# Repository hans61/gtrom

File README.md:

# Gigatron ROM Adapter
This is my first attempt for a simple ROM adapter for the Gigatron TTL. There are two good reasons for this.
The first is, there is no inexpensive ZIF socket that fits directly on the mainboard. If you use a turned socket on the mainboard and turned pins for the adapter, then it adds a ZIF socket to the Gigatron.
My second problem is that to test different software I often have to change the ROM. This is inconvenient because I have to remove the cover from my Gigatron case each time.
The adapter allows the use of a 256k x16 EPROM. This allows, via a switch or jumper, switching 4 different ROM's. 
One possible EPROM is the 27C4002. I found it in China and at the local dealer. (https://www.reichelt.de/eprom-4-mb-256-k-x-16-4-5-5-5-v-fdip-40-27c4002-100-p1930.html?&nbc=1)
In China I also found the W27C4096, a pin compatible EEPROM.

Theoretically, a simple ROM banking would also be possible in this way to extend the Gigatron ROM.

I have tested the ROM switch with the 27C4002. The 27C4002 can be programmed with the TL866II or successor devices. With both switches in the off position, the original Gigatron ROM can also be used.

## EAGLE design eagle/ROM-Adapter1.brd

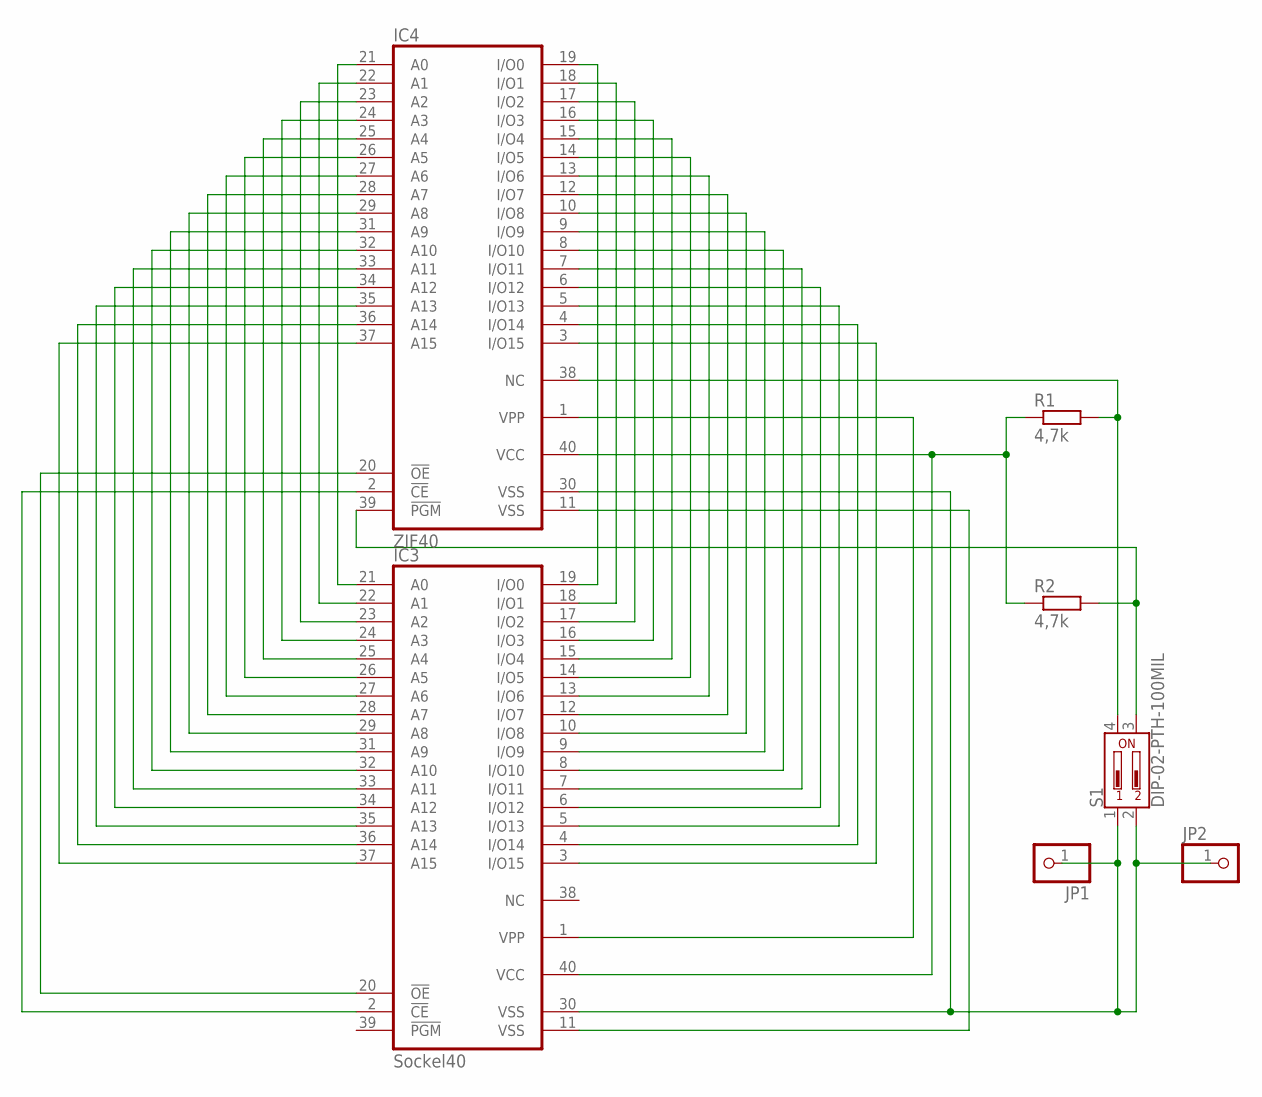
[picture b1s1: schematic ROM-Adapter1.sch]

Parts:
IC3: Sockel40; DIL40
IC4: ZIF40; MEMORY-HITACHI_ZIF40
JP1, JP2: PINHD-1X1; 1X01
R1, R2: 4,7k; 0207/10
S1: DIP-02-PTH-100MIL; DIPSWITCH-02-209-2LPST

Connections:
unnamed: IC3.21 (A0), IC4.21 (A0)
unnamed: IC3.22 (A1), IC4.22 (A1)
unnamed: IC3.23 (A2), IC4.23 (A2)
unnamed: IC3.24 (A3), IC4.24 (A3)
unnamed: IC3.25 (A4), IC4.25 (A4)
unnamed: IC3.26 (A5), IC4.26 (A5)
unnamed: IC3.27 (A6), IC4.27 (A6)
unnamed: IC3.28 (A7), IC4.28 (A7)
unnamed: IC3.29 (A8), IC4.29 (A8)
unnamed: IC3.31 (A9), IC4.31 (A9)
unnamed: IC3.32 (A10), IC4.32 (A10)
unnamed: IC3.33 (A11), IC4.33 (A11)
unnamed: IC3.34 (A12), IC4.34 (A12)
unnamed: IC3.35 (A13), IC4.35 (A13)
unnamed: IC3.36 (A14), IC4.36 (A14)
unnamed: IC3.37 (A15), IC4.37 (A15)
unnamed: IC3.20 (!OE), IC4.20 (!OE)
unnamed: IC3.2 (!CE), IC4.2 (!CE)
unnamed: IC4.38 (NC), R1.2, S1.4
unnamed: IC3.19 (I/O0), IC4.19 (I/O0)
unnamed: IC3.18 (I/O1), IC4.18 (I/O1)
unnamed: IC3.17 (I/O2), IC4.17 (I/O2)
unnamed: IC3.16 (I/O3), IC4.16 (I/O3)
unnamed: IC3.15 (I/O4), IC4.15 (I/O4)
unnamed: IC3.14 (I/O5), IC4.14 (I/O5)
unnamed: IC3.13 (I/O6), IC4.13 (I/O6)
unnamed: IC3.12 (I/O7), IC4.12 (I/O7)
unnamed: IC3.10 (I/O8), IC4.10 (I/O8)
unnamed: IC3.9 (I/O9), IC4.9 (I/O9)
unnamed: IC3.8 (I/O10), IC4.8 (I/O10)
unnamed: IC3.7 (I/O11), IC4.7 (I/O11)
unnamed: IC3.6 (I/O12), IC4.6 (I/O12)
unnamed: IC3.5 (I/O13), IC4.5 (I/O13)
unnamed: IC3.4 (I/O14), IC4.4 (I/O14)
unnamed: IC3.3 (I/O15), IC4.3 (I/O15)
unnamed: IC4.39 (!PGM), R2.2, S1.3
unnamed: IC3.1 (VPP), IC4.1 (VPP)
unnamed: IC3.40 (VCC), IC4.40 (VCC), R1.1, R2.1
unnamed: IC3.11 (VSS), IC4.11 (VSS)
unnamed: IC3.30 (VSS), IC4.30 (VSS), JP1.1, JP2.1, S1.1, S1.2

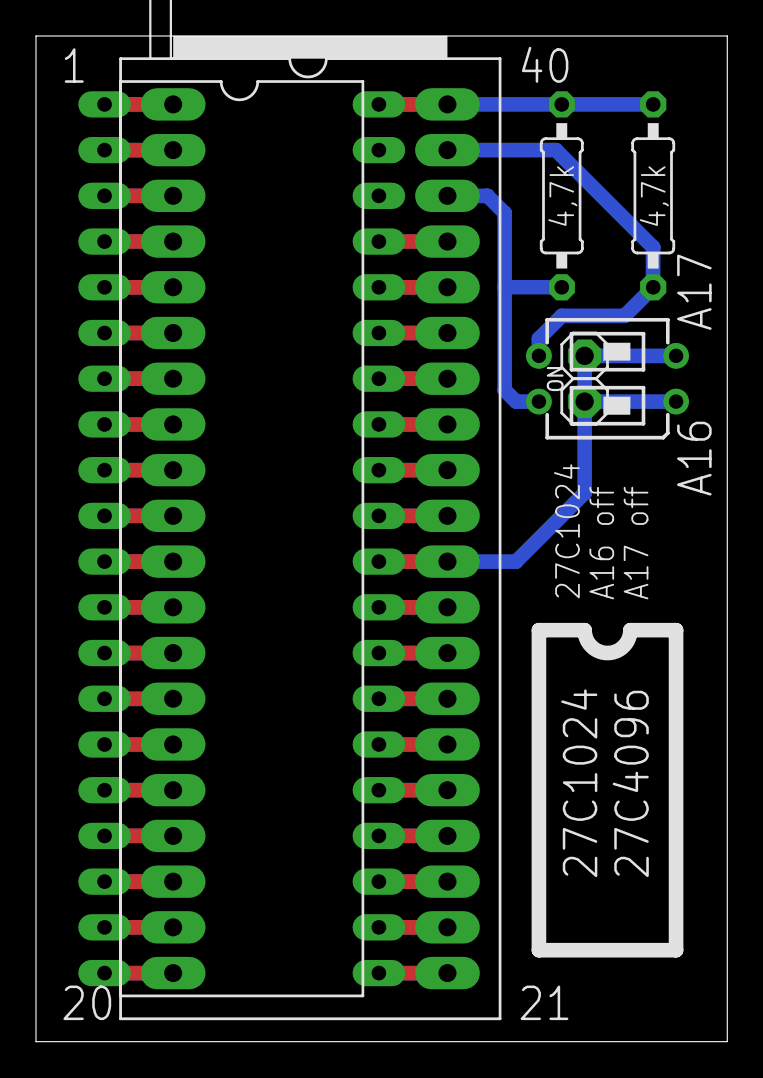
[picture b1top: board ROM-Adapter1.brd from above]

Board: 2 copper layers, 38.4 x 55.9 mm, 7 parts (0 on the bottom side), 40 nets.

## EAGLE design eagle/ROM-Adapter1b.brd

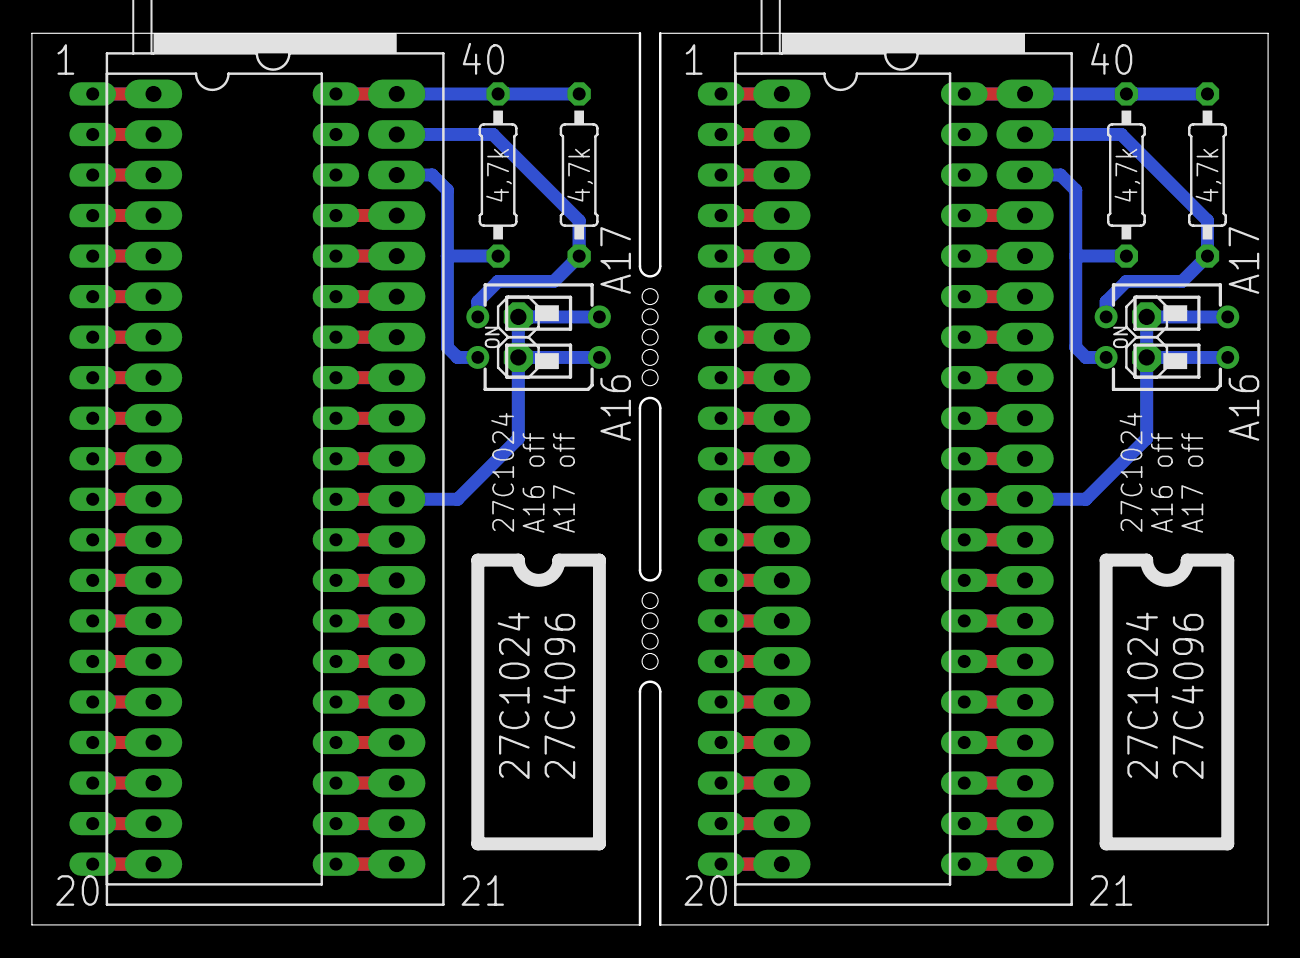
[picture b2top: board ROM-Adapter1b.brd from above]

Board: 2 copper layers, 77.5 x 55.9 mm, 14 parts (0 on the bottom side), 80 nets.

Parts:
IC1, IC3: Sockel40; DIL40
IC2, IC4: ZIF40; MEMORY-HITACHI_ZIF40
JP1, JP2, JP3, JP4: 1X01
R1, R2, R3, R4: 4,7k; 0207/10
S1, S2: DIP-02-PTH-100MIL; DIPSWITCH-02-209-2LPST

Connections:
unnamed: IC3.21, IC4.21
unnamed: IC3.22, IC4.22
unnamed: IC3.23, IC4.23
unnamed: IC3.24, IC4.24
unnamed: IC3.25, IC4.25
unnamed: IC3.26, IC4.26
unnamed: IC3.27, IC4.27
unnamed: IC3.28, IC4.28
unnamed: IC3.29, IC4.29
unnamed: IC3.31, IC4.31
unnamed: IC3.32, IC4.32
unnamed: IC3.33, IC4.33
unnamed: IC3.34, IC4.34
unnamed: IC3.35, IC4.35
unnamed: IC3.36, IC4.36
unnamed: IC3.37, IC4.37
unnamed: IC3.20, IC4.20
unnamed: IC3.2, IC4.2
unnamed: IC4.38, R1.2, S1.4
unnamed: IC3.19, IC4.19
unnamed: IC3.18, IC4.18
unnamed: IC3.17, IC4.17
unnamed: IC3.16, IC4.16
unnamed: IC3.15, IC4.15
unnamed: IC3.14, IC4.14
unnamed: IC3.13, IC4.13
unnamed: IC3.12, IC4.12
unnamed: IC3.10, IC4.10
unnamed: IC3.9, IC4.9
unnamed: IC3.8, IC4.8
unnamed: IC3.7, IC4.7
unnamed: IC3.6, IC4.6
unnamed: IC3.5, IC4.5
unnamed: IC3.4, IC4.4
unnamed: IC3.3, IC4.3
unnamed: IC4.39, R2.2, S1.3
unnamed: IC3.1, IC4.1
unnamed: IC3.40, IC4.40, R1.1, R2.1
unnamed: IC1.21, IC2.21
unnamed: IC3.11, IC4.11
unnamed: IC1.22, IC2.22
unnamed: IC3.30, IC4.30, JP1.1, JP2.1, S1.1, S1.2
unnamed: IC1.23, IC2.23
unnamed: IC1.24, IC2.24
unnamed: IC1.25, IC2.25
unnamed: IC1.26, IC2.26
unnamed: IC1.27, IC2.27
unnamed: IC1.28, IC2.28
unnamed: IC1.29, IC2.29
unnamed: IC1.31, IC2.31
unnamed: IC1.32, IC2.32
unnamed: IC1.33, IC2.33
unnamed: IC1.34, IC2.34
unnamed: IC1.35, IC2.35
unnamed: IC1.36, IC2.36
unnamed: IC1.37, IC2.37
unnamed: IC1.20, IC2.20
unnamed: IC1.2, IC2.2
unnamed: IC1.19, IC2.19
unnamed: IC1.18, IC2.18
unnamed: IC1.17, IC2.17
unnamed: IC1.16, IC2.16
unnamed: IC1.15, IC2.15
unnamed: IC1.14, IC2.14
unnamed: IC1.13, IC2.13
unnamed: IC1.12, IC2.12
unnamed: IC1.10, IC2.10
unnamed: IC1.9, IC2.9
unnamed: IC1.8, IC2.8
unnamed: IC1.7, IC2.7
unnamed: IC1.6, IC2.6
unnamed: IC1.5, IC2.5
unnamed: IC1.4, IC2.4
unnamed: IC1.3, IC2.3
unnamed: IC1.1, IC2.1
unnamed: IC1.40, IC2.40, R3.1, R4.1
unnamed: IC1.11, IC2.11
unnamed: IC2.38, R3.2, S2.4
unnamed: IC2.39, R4.2, S2.3
unnamed: IC1.30, IC2.30, JP3.1, JP4.1, S2.1, S2.2

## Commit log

2023-04-15 initial
2023-04-24 Image changed
2023-04-24 schematic added

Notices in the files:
parts and their libraries:
SparkFun-Switches: Licensing: Creative Commons ShareAlike 4.0 International - https://creativecommons.org/licenses/by-sa/4.0
